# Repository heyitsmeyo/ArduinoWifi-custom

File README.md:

# ArduinoWifi-custom
A cutsom arduino uno pcb design that supports Wi-Fi and SD card reader 

# if you like the project , you can donate us for more : 

    https://ko-fi.com/heyitsmeyo

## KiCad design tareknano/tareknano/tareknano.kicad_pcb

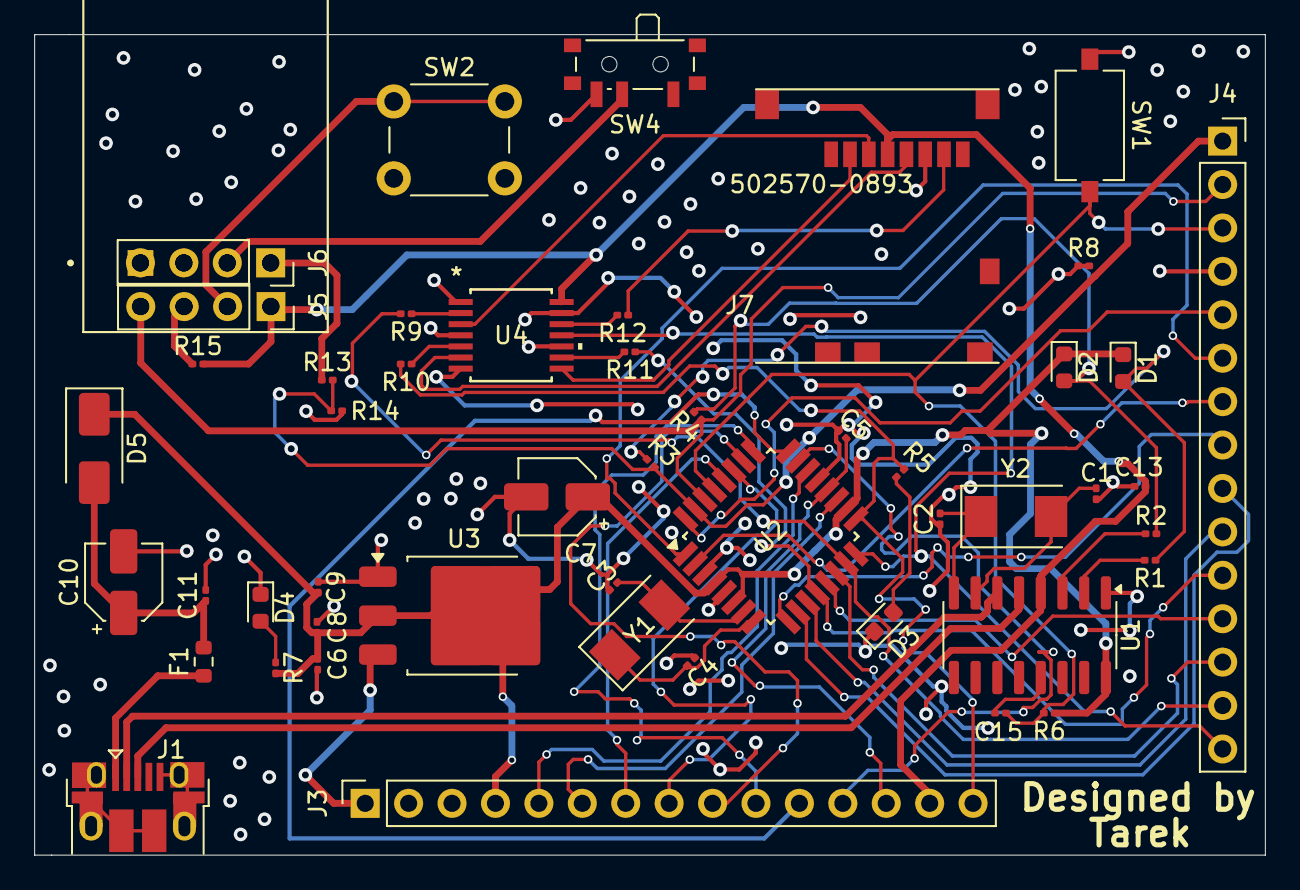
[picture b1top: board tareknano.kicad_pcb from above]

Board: 2 copper layers, 72.0 x 48.0 mm, 50 parts (0 on the bottom side), 56 nets.

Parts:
C1, C2, C3, C4: 22pf; C_0201_0603Metric
C5, C11, C13, C15: 100nf; C_0201_0603Metric
C6, C8, C9: 1uf; C_0201_0603Metric
C7, C10: 4.7uf; CP_Elec_4x5.8
D1, D2, D3, D4: LED; LED_0603_1608Metric
D5: SS13; D_SMA
F1: Fuse; R_0603_1608Metric
J1: USB_B_Micro; USB_Micro-B_Amphenol_10103594-0001LF_Horizontal
J3, J4: Conn_01x15_Pin; PinSocket_1x15_P2.54mm_Vertical
J5, J6: Conn_01x04_Socket; PinSocket_1x04_P2.54mm_Vertical
J7: 502570-0893; MOLEX_502570-0893
R1, R2, R3, R4, R5, R7, R8, R14: 1k; R_0201_0603Metric
R6, R15: 10k; R_0201_0603Metric
R9, R10, R11, R12: 3.3k; R_0201_0603Metric
R13: 2k; R_0201_0603Metric
SW1: SW_Push; SW_Tactile_SPST_NO_Straight_CK_PTS636Sx25SMTRLFS
SW2: SW_Push_Dual; SW_PUSH_6mm
SW4: SW_SPDT; SW_SPDT_PCM12
U1: CH340G; SOIC-16_3.9x9.9mm_P1.27mm
U2: ATmega328P-A; TQFP-32_7x7mm_P0.8mm
U3: LM1117DT-5.0; TO-252-3_TabPin2
U4: 74LVC125APW_118; TSSOP14_SOT402-1_NEX
U5: ESP-01; MODULE_ESP-01
Y1: Crystal; Crystal_SMD_Abracon_ABM3-2Pin_5.0x3.2mm
Y2: 12Mhz; Crystal_SMD_Abracon_ABM3-2Pin_5.0x3.2mm

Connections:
3V3: C13.1, J3.14, J5.1, J7.4 (VDD), R15.2, U1.4 (V3), U4.14 (VCC), U5.5 (VCC)
5V: C6.2, C7.1, C8.2, C9.2, D1.1 (K), D2.1 (K), D5.1 (K), J3.4, R6.1, R7.2, U1.16 (VCC), U2.4 (VCC), U2.6 (VCC), U2.18 (AVCC), U3.2 (VO)
/A0: J3.12, U2.23 (PC0)
/A1: J3.11, U2.24 (PC1)
/A2: J3.10, U2.25 (PC2)
/A3: J3.9, U2.26 (PC3)
/A4: J3.8, U2.27 (PC4)
/A5: J3.7, U2.28 (PC5)
/A6: J3.6, U2.19 (ADC6)
/A7: J3.5, U2.22 (ADC7)
/AREF: C5.2, J3.13, U2.20 (AREF)
/CH_PD: J5.3, R15.1, U5.7 (CH_PD)
/CLK: J7.5 (CLK), U4.6 (2Y)
/CMD: J7.3 (CMD), U4.3 (1Y)
/D0/RX: J4.2, J5.4, R4.2, U2.30 (PD0), U5.8 (TXD)
/D1/TX: J4.1, R3.2, R13.2, R14.1, U2.31 (PD1)
/D2: J4.5, U2.32 (PD2)
/D3: J4.6, U2.1 (PD3)
/D4: J4.7, U2.2 (PD4)
/D5: J4.8, U2.9 (PD5)
/D6: J4.9, U2.10 (PD6)
/D7: J4.10, U2.11 (PD7)
/D8: J4.11, R11.1, U2.12 (PB0)
/D9: J4.12, U2.13 (PB1)
/D10: J4.13, U2.14 (PB2)
/D11/MOSI: J4.14, R9.2, U2.15 (PB3)
/D12/MISO: J4.15, U2.16 (PB4), U4.11 (4Y)
/D13/SCK: J3.15, R5.2, R10.2, U2.17 (PB5)
/D+: J1.3 (D+), U1.5 (UD+)
/D-: J1.2 (D-), U1.6 (UD-)
/DAT0: J7.7 (DAT0), R12.1
/DAT3/CD: J7.2 (CD/DAT3), U4.8 (3Y)
/GPIO0: J6.2, SW4.2 (B), U5.3 (GPIO0)
/GPIO2: J6.3, U5.2 (GPIO2)
/RST: J5.2, SW2.1, U5.6 (~RST)
/RXD esp: J6.1, R13.1, U5.4 (RXD)
GND: C1.2, C2.2, C3.2, C4.2, C5.1, C6.1, C7.2, C8.1, C9.1, C10.2, C11.2, C13.2, D3.1 (K), D4.1 (K), J1.5 (GND), J1.6 (Shield), J3.2, J3.3, J4.4, J6.4, J7.6 (VSS), R8.1, R8.2, R14.2, SW1.1, SW2.2, SW4.3 (C), U1.1 (GND), U2.3 (GND), U2.5 (GND), U2.21 (GND), U3.1 (GND), U4.1 (*1OE), U4.4 (*2OE), U4.7 (GND), U4.10 (*3OE), U4.13 (*4OE), U5.1 (GND)
unnamed: D3.2 (A), R5.1
unnamed: D4.2 (A), R7.1
unnamed: F1.1, J1.1 (VBUS)
unnamed: R2.1, U1.3 (RXD)
unnamed: R1.2, U1.2 (TXD)
unnamed: C1.1, U1.7 (XI), Y2.2
unnamed: C2.1, U1.8 (XO), Y2.1
unnamed: C15.1, U1.13 (~DTR)
unnamed: C3.1, U2.7 (XTAL1/PB6), Y1.2
unnamed: C4.1, U2.8 (XTAL2/PB7), Y1.1
unnamed: R9.1, U4.2 (1A)
unnamed: R10.1, U4.5 (2A)
unnamed: R11.2, U4.9 (3A)
unnamed: R12.2, U4.12 (4A)
RESET: C15.2, J4.3, R6.2, SW1.2, U2.29 (~RESET/PC6)
RX: D2.2 (A), R2.2, R4.1
TX: D1.2 (A), R1.1, R3.1
VIN: J3.1, U3.3 (VI)
VUSB: C10.1, C11.1, D5.2 (A), F1.2

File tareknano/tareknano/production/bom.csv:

Designator,Footprint,Quantity,Value,LCSC Part #
"C1, C2, C3, C4",0201,4,22pf,
"C10, C7",CP_Elec_4x5.8,2,4.7uf,
"C11, C13, C15, C5",0201,4,100nf,
"C6, C8, C9",0201,3,1uf,
"D1, D2, D3, D4",0603,4,LED,
D5,D_SMA,1,SS13,
F1,0603,1,Fuse,
J1,USB_Micro-B_Amphenol_10103594-0001LF_Horizontal,1,USB_B_Micro,
"J3, J4",PinSocket_1x15_P2.54mm_Vertical,2,Conn_01x15_Pin,
"J5, J6",PinSocket_1x04_P2.54mm_Vertical,2,Conn_01x04_Socket,
J7,MOLEX_502570-0893,1,502570-0893,
"R1, R14, R2, R3, R4, R5, R7, R8",0201,8,1k,
"R10, R11, R12, R9",0201,4,3.3k,
R13,0201,1,2k,
"R15, R6",0201,2,10k,
SW1,SW_Tactile_SPST_NO_Straight_CK_PTS636Sx25SMTRLFS,1,SW_Push,
SW2,SW_PUSH_6mm,1,SW_Push_Dual,
SW4,SW_SPDT_PCM12,1,SW_SPDT,
U1,SOIC-16_3.9x9.9mm_P1.27mm,1,CH340G,
U2,TQFP-32_7x7mm_P0.8mm,1,ATmega328P-A,
U3,TO-252-3_TabPin2,1,LM1117DT-5.0,
U4,TSSOP14_SOT402-1_NEX,1,74LVC125APW_118,
U5,MODULE_ESP-01,1,ESP-01,
Y1,Crystal_SMD_Abracon_ABM3-2Pin_5.0x3.2mm,1,Crystal,
Y2,Crystal_SMD_Abracon_ABM3-2Pin_5.0x3.2mm,1,12Mhz,
